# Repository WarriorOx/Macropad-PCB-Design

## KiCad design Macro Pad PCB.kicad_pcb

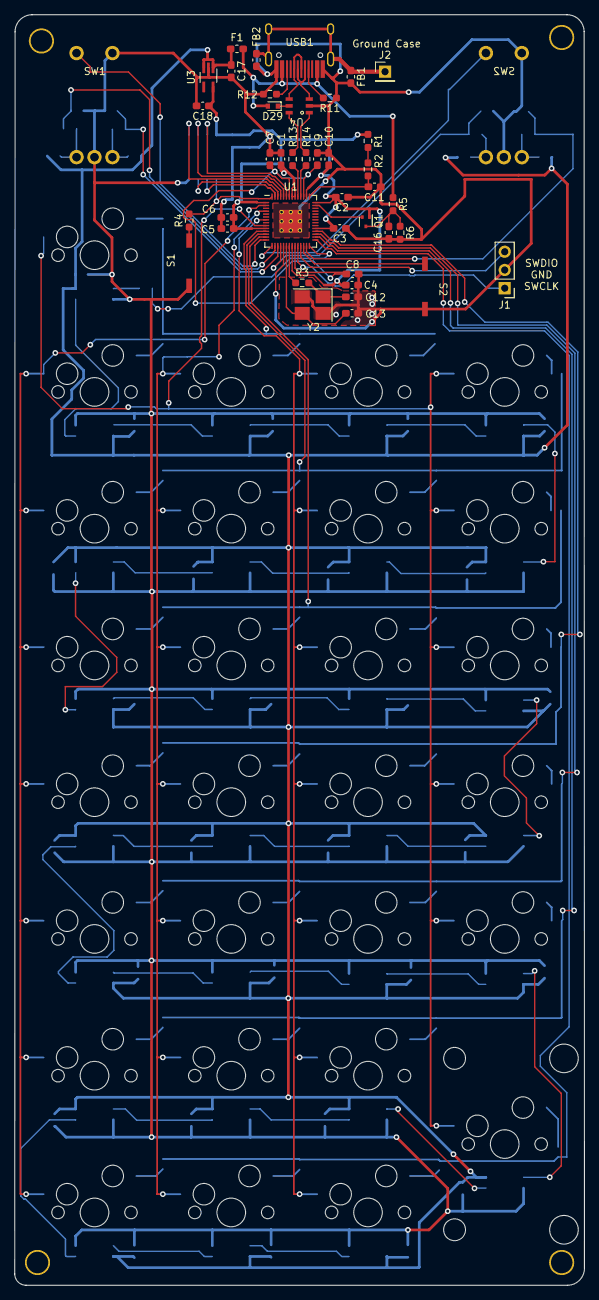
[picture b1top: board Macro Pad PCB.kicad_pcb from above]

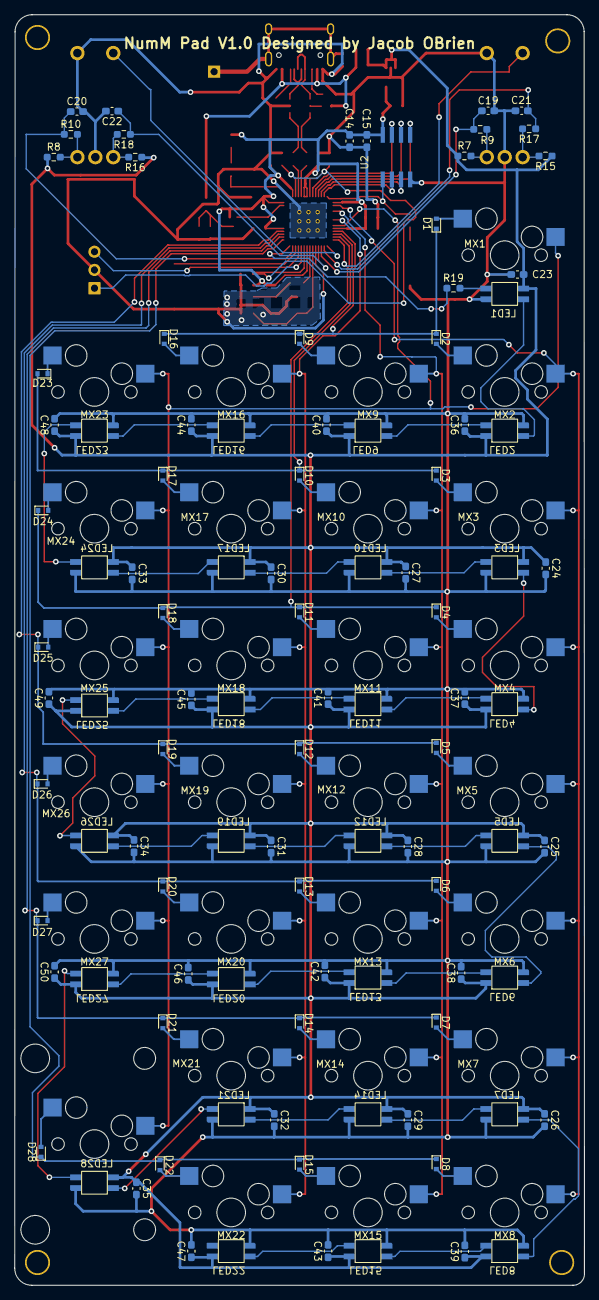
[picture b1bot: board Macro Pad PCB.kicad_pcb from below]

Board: 2 copper layers, 79.4 x 177.0 mm, 174 parts (72 on the bottom side), 110 nets.

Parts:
C1, C2, C3, C4, C5, C6, C7, C8, C15: 100n; C_0603_1608Metric_Pad1.08x0.95mm_HandSolder
C9, C10, C11, C14: 2.2u; C_0603_1608Metric_Pad1.08x0.95mm_HandSolder
C12, C13: 15p; C_0603_1608Metric_Pad1.08x0.95mm_HandSolder
C16: 1n; C_0603_1608Metric_Pad1.08x0.95mm_HandSolder
C17, C18: 1uF; C_0603_1608Metric_Pad1.08x0.95mm_HandSolder
C19, C20, C21, C22: 0.01uF; C_0603_1608Metric_Pad1.08x0.95mm_HandSolder
C23, C24, C25, C26, C27, C28, C29, C30, C31, C32, C33, C34, C35, C36, C37, C38, C39, C40, C41, C42, C43, C44, C45, C46, C47, C48, C49, C50: 100nF; C_0603_1608Metric_Pad1.08x0.95mm_HandSolder
D1, D2, D3, D4, D5, D6, D7, D8, D9, D10, D11, D12, D13, D14, D15, D16, D17, D18, D19, D20, D21, D22, D23, D24, D25, D26, D27, D28: D_Small; D_SOD-523
D29: 1N4148; D_SOD-523
F1: 500mA?; Fuse_0603_1608Metric_Pad1.05x0.95mm_HandSolder
FB1, FB2: 70@100MHz; L_0603_1608Metric_Pad1.05x0.95mm_HandSolder
H1, H2, H3, H4: 3mm_Hole; 3mm Hole
J1: Debug; PinHeader_1x03_P2.54mm_Vertical
J2: SHIELD CON; PinHeader_1x01_P2.54mm_Vertical
LED1, LED2, LED3, LED4, LED5, LED6, LED7, LED8, LED9, LED10, LED11, LED12, LED13, LED14, LED15, LED16, LED17, LED18, LED19, LED20, LED21, LED22, LED23, LED24, LED25, LED26, LED27, LED28: SK812_Mini-E; SK812 Mini-E
MX1, MX2, MX3, MX4, MX5, MX6, MX7, MX8, MX9, MX10, MX11, MX12, MX13, MX14, MX15, MX16, MX17, MX18, MX19, MX20, MX21, MX22, MX23, MX24, MX25, MX26, MX27: MX-NoLED; MXOnly-1U-Hotswap
MX28: MX-NoLED; MXOnly-2U-Hotswap-VerticalStabilizers
Q1: DMG1012T; SOT-523
R1: 200R; R_0603_1608Metric_Pad0.98x0.95mm_HandSolder
R2: 1R; R_0603_1608Metric_Pad0.98x0.95mm_HandSolder
R3, R4: 1k; R_0603_1608Metric_Pad0.98x0.95mm_HandSolder
R5: 200k; R_0603_1608Metric_Pad0.98x0.95mm_HandSolder
R6: 100k; R_0603_1608Metric_Pad0.98x0.95mm_HandSolder
R7, R8, R9, R10, R11, R12, R15, R16, R17, R18: 5.1k; R_0603_1608Metric_Pad0.98x0.95mm_HandSolder
R13, R14: 27; R_0603_1608Metric_Pad0.98x0.95mm_HandSolder
R19: 330; R_0603_1608Metric_Pad0.98x0.95mm_HandSolder
S1, S2: Reset_Switch; Reset Switch
SW1, SW2: PEC11R-4015F-S0024
U1: RP2040; RP2040-QFN-56
U2: W25Q16JVSNIQ; SOIC 150-mil
U3: MIC5365-3.3YC5-TR; SOT-353_SC-70-5_Handsoldering
U4: IP4234CZ6; SOT-457
USB1: HRO-TYPE-C-31-M-12; HRO-TYPE-C-31-M-12-HandSoldering
Y2: 12 MHz; Crystal_SMD_3225-4Pin_3.2x2.5mm_HandSoldering

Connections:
+1V1: C7.2, C8.2, C9.2, U1.23 (DVDD), U1.45 (VREG_VOUT), U1.50 (DVDD)
+3.3V: C1.2, C2.2, C3.2, C4.2, C5.2, C6.2, C10.2, C14.1, C15.1, C18.1, Q1.1 (G), R1.1, U1.1 (IOVDD), U1.10 (IOVDD), U1.22 (IOVDD), U1.33 (IOVDD), U1.42 (IOVDD), U1.44 (VREG_IN), U1.48 (USB_VDD), U1.49 (IOVDD), U2.8 (Vcc), U3.5 (VOUT)
+5V: C17.1, C23.1, C24.1, C25.1, C26.1, C27.1, C28.1, C29.1, C30.1, C31.1, C32.1, C33.1, C34.1, C35.1, C36.1, C37.1, C38.1, C39.1, C40.1, C41.1, C42.1, C43.1, C44.1, C45.1, C46.1, C47.1, C48.1, C49.1, C50.1, F1.1, LED1.1 (VDD), LED2.1 (VDD), LED3.1 (VDD), LED4.1 (VDD), LED5.1 (VDD), LED6.1 (VDD), LED7.1 (VDD), LED8.1 (VDD), LED9.1 (VDD), LED10.1 (VDD), LED11.1 (VDD), LED12.1 (VDD), LED13.1 (VDD), LED14.1 (VDD), LED15.1 (VDD), LED16.1 (VDD), LED17.1 (VDD), LED18.1 (VDD), LED19.1 (VDD), LED20.1 (VDD), LED21.1 (VDD), LED22.1 (VDD), LED23.1 (VDD), LED24.1 (VDD), LED25.1 (VDD), LED26.1 (VDD), LED27.1 (VDD), LED28.1 (VDD), R7.1, R8.1, R15.1, R16.1, U3.1 (VIN), U3.3 (EN)
Col 1: MX2.1 (COL), MX3.1 (COL), MX4.1 (COL), MX5.1 (COL), MX6.1 (COL), MX7.1 (COL), MX8.1 (COL), U1.2 (GPIO0)
Col 2: MX9.1 (COL), MX10.1 (COL), MX11.1 (COL), MX12.1 (COL), MX13.1 (COL), MX14.1 (COL), MX15.1 (COL), U1.4 (GPIO2)
Col 3: MX16.1 (COL), MX17.1 (COL), MX18.1 (COL), MX19.1 (COL), MX20.1 (COL), MX21.1 (COL), MX22.1 (COL), U1.7 (GPIO5)
Col 4: MX1.1 (COL), MX23.1 (COL), MX24.1 (COL), MX25.1 (COL), MX26.1 (COL), MX27.1 (COL), MX28.1 (COL), U1.9 (GPIO7)
ENC1 A: C21.1, R17.1, U1.16 (GPIO13)
ENC1 B: C19.1, R9.1, U1.17 (GPIO14)
ENC2 A: C22.1, R18.1, U1.18 (GPIO15)
ENC2 B: C20.1, R10.1, U1.27 (GPIO16)
ENC SW1: SW1.S1, U1.14 (GPIO11)
ENC SW2: SW2.S1, U1.15 (GPIO12)
Earth: C1.1, C2.1, C3.1, C4.1, C5.1, C6.1, C7.1, C8.1, C9.1, C10.1, C11.2, C12.2, C13.2, C14.2, C15.2, C16.2, C17.2, C18.2, C19.2, C20.2, C21.2, C22.2, C23.2, C24.2, C25.2, C26.2, C27.2, C28.2, C29.2, C30.2, C31.2, C32.2, C33.2, C34.2, C35.2, C36.2, C37.2, C38.2, C39.2, C40.2, C41.2, C42.2, C43.2, C44.2, C45.2, C46.2, C47.2, C48.2, C49.2, C50.2, FB1.2, FB2.2, J1.2, LED1.3 (GND), LED2.3 (GND), LED3.3 (GND), LED4.3 (GND), LED5.3 (GND), LED6.3 (GND), LED7.3 (GND), LED8.3 (GND), LED9.3 (GND), LED10.3 (GND), LED11.3 (GND), LED12.3 (GND), LED13.3 (GND), LED14.3 (GND), LED15.3 (GND), LED16.3 (GND), LED17.3 (GND), LED18.3 (GND), LED19.3 (GND), LED20.3 (GND), LED21.3 (GND), LED22.3 (GND), LED23.3 (GND), LED24.3 (GND), LED25.3 (GND), LED26.3 (GND), LED27.3 (GND), LED28.3 (GND), R6.2, R11.1, R12.2, S1.1 (S1), S2.2 (S2), SW1.C, SW1.S2, SW2.C, SW2.S2, U1.19 (TESTEN), U1.57 (GND), U2.4 (GND), U3.2 (GND), U4.2 (GND), USB1.1 (GND), USB1.12 (GND), Y2.2, Y2.4
GPIO29_ADC3: Q1.2 (S), U1.41 (GPIO29_ADC3)
LED DIN: R19.1, U1.28 (GPIO17)
unnamed: C11.1, R2.2, U1.43 (ADC_AVDD)
unnamed: C12.1, R3.2, Y2.1
unnamed: C16.1, Q1.3 (D), R5.2, R6.1
unnamed: D1.2 (A), MX1.2 (ROW)
unnamed: D2.2 (A), MX2.2 (ROW)
unnamed: D3.2 (A), MX3.2 (ROW)
unnamed: D4.2 (A), MX4.2 (ROW)
unnamed: D5.2 (A), MX5.2 (ROW)
unnamed: D6.2 (A), MX6.2 (ROW)
unnamed: D7.2 (A), MX7.2 (ROW)
unnamed: D8.2 (A), MX8.2 (ROW)
unnamed: D9.2 (A), MX9.2 (ROW)
unnamed: D10.2 (A), MX10.2 (ROW)
unnamed: D11.2 (A), MX11.2 (ROW)
unnamed: D12.2 (A), MX12.2 (ROW)
unnamed: D13.2 (A), MX13.2 (ROW)
unnamed: D14.2 (A), MX14.2 (ROW)
unnamed: D15.2 (A), MX15.2 (ROW)
unnamed: D16.2 (A), MX16.2 (ROW)
unnamed: D17.2 (A), MX17.2 (ROW)
unnamed: D18.2 (A), MX18.2 (ROW)
unnamed: D19.2 (A), MX19.2 (ROW)
unnamed: D20.2 (A), MX20.2 (ROW)
unnamed: D21.2 (A), MX21.2 (ROW)
unnamed: D22.2 (A), MX22.2 (ROW)
unnamed: D23.1 (K), MX23.2 (ROW)
unnamed: D24.2 (A), MX24.2 (ROW)
unnamed: D25.2 (A), MX25.2 (ROW)
unnamed: D26.2 (A), MX26.2 (ROW)
unnamed: D27.2 (A), MX27.2 (ROW)
unnamed: D28.2 (A), MX28.2 (ROW)
unnamed: D29.1 (K), U4.5 (Vsupply)
unnamed: FB1.1, FB2.1, J2.1, USB1.13 (SHIELD)
unnamed: LED1.2 (DOUT), LED2.4 (DIN)
unnamed: LED1.4 (DIN), R19.2
unnamed: LED2.2 (DOUT), LED9.4 (DIN)
unnamed: LED3.2 (DOUT), LED4.4 (DIN)
unnamed: LED5.2 (DOUT), LED6.4 (DIN)
unnamed: LED7.2 (DOUT), LED8.4 (DIN)
unnamed: LED3.4 (DIN), LED10.2 (DOUT)
unnamed: LED10.4 (DIN), LED17.2 (DOUT)
unnamed: LED11.2 (DOUT), LED18.4 (DIN)
unnamed: LED4.2 (DOUT), LED11.4 (DIN)
unnamed: LED5.4 (DIN), LED12.2 (DOUT)
unnamed: LED12.4 (DIN), LED19.2 (DOUT)
unnamed: LED13.2 (DOUT), LED20.4 (DIN)
unnamed: LED6.2 (DOUT), LED13.4 (DIN)
unnamed: LED7.4 (DIN), LED14.2 (DOUT)
unnamed: LED14.4 (DIN), LED21.2 (DOUT)
unnamed: LED15.2 (DOUT), LED22.4 (DIN)
unnamed: LED8.2 (DOUT), LED15.4 (DIN)
unnamed: LED16.2 (DOUT), LED23.4 (DIN)
unnamed: LED9.2 (DOUT), LED16.4 (DIN)
unnamed: LED17.4 (DIN), LED24.2 (DOUT)
unnamed: LED18.2 (DOUT), LED25.4 (DIN)
unnamed: LED19.4 (DIN), LED26.2 (DOUT)
unnamed: LED20.2 (DOUT), LED27.4 (DIN)
unnamed: LED21.4 (DIN), LED28.2 (DOUT)
unnamed: LED23.2 (DOUT), LED24.4 (DIN)
unnamed: LED25.2 (DOUT), LED26.4 (DIN)
unnamed: LED27.2 (DOUT), LED28.4 (DIN)
unnamed: R1.2, R2.1
unnamed: R4.1, S1.2 (S2)
unnamed: R7.2, R9.2, SW1.B
unnamed: R8.2, R10.2, SW2.B
unnamed: R11.2, USB1.4 (CC1)
unnamed: R12.1, USB1.10 (CC2)
unnamed: R15.2, R17.2, SW1.A
unnamed: R16.2, R18.2, SW2.A
QSPI_SCLK: U1.52 (QSPI_SCLK), U2.6 (CLK)
QSPI_SD0: U1.53 (QSPI_SD0), U2.5 (DI(IO_0))
QSPI_SD1: U1.55 (QSPI_SD1), U2.2 (DO(IO1))
QSPI_SD2: U1.54 (QSPI_SD2), U2.3 (/WP(IO2))
QSPI_SD3: U1.51 (QSPI_SD3), U2.7 (/Reset)
QSPI_SS: R4.2, U1.56 (QSPI_SS), U2.1 (/CS)
RUN: S2.1 (S1), U1.26 (RUN)
Row 1: D1.1 (K), D2.1 (K), D9.1 (K), D16.1 (K), U1.11 (GPIO8)
Row 2: D3.1 (K), D10.1 (K), D17.1 (K), D23.2 (A), U1.12 (GPIO9)
Row 3: D4.1 (K), D11.1 (K), D18.1 (K), D24.1 (K), U1.13 (GPIO10)
Row 4: D5.1 (K), D12.1 (K), D19.1 (K), D25.1 (K), U1.32 (GPIO21)
Row 5: D6.1 (K), D13.1 (K), D20.1 (K), D26.1 (K), U1.31 (GPIO20)
Row 6: D7.1 (K), D14.1 (K), D21.1 (K), D27.1 (K), U1.30 (GPIO19)
Row 7: D8.1 (K), D15.1 (K), D22.1 (K), D28.1 (K), U1.29 (GPIO18)
SWCLK: J1.1, U1.24 (SWCLK)
SWDIO: J1.3, U1.25 (SWD)
USB_data+: R13.1, U1.47 (USB_DP)
USB_data-: R14.1, U1.46 (USB_DM)
VCC: D29.2 (A), F1.2, R5.1, USB1.2 (VBUS), USB1.11 (VBUS)
Xin: C13.1, U1.20 (XIN), Y2.3
Xout: R3.1, U1.21 (XOUT)
d2N: R14.2, U4.1 (ESD_CH1)
d2P: R13.2, U4.6 (ESD_CH2)
dN: U4.3 (ESD_CH1.2), USB1.5 (DN2), USB1.7 (DN1)
dP: U4.4 (ESD_CH2.2), USB1.6 (DP1), USB1.8 (DP2)

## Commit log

2022-09-17 Added Libraries
    Added Various libraries including RP2040 symbols and USB-C connectors
2022-09-17 Connected Libraries
2022-09-17 Began Schematic Layout
2022-10-03 Added DC-DC Converter
2022-10-21 Added Key Matrix
2022-12-23 Schematic Finallized
    Added ESD Protection to USB input and RGB LEDs
2023-01-05 Layout Roughed in, routing started
2023-01-05 Routing Continued
2023-01-07 Routing Finished and ESD Protection Enhanced
